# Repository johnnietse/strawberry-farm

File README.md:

# 🌿 G.O.S. - Greenhouse Operating System
## High-Throughput Plant Phenotyping Platform

**Illuminate & Automate: Reinforcement Learning + IoT Sensor Array for LED-Steered Transpiration in Greenhouse Strawberries**

---

## 📋 Table of Contents

1. [What is G.O.S.?](#-what-is-gos)
2. [System Architecture](#-system-architecture)
3. [Data Flow Workflow](#-data-flow-workflow)
4. [Quick Start](#-quick-start)
5. [Testing & Verification](#-testing--verification)
6. [File Reference](#-file-reference)
7. [API Endpoints](#-api-endpoints)
8. [Hardware Integration](#-hardware-integration)

---

## 🎯 What is G.O.S.?

G.O.S. is an **open-source phenotyping platform** that transforms raw greenhouse sensor data into actionable plant insights:

| Feature | Description |
|:---|:---|
| **40 Wireless Nodes** | nRF52840 sensors (Thread mesh) |
| **VPD Calculation** | Real-time vapor pressure deficit |
| **Transpiration** | Penman-Monteith estimation |
| **Stress Detection** | Multi-factor scoring (0-100) |
| **LED Control** | RL-based spectral recommendations |
| **ML Pipeline** | 5-source temporal synchronization |

---

## 🏗️ System Architecture

### Service Topology (12 Docker Containers)

```
┌─────────────────────────────────────────────────────────────┐
│                    USER INTERFACE LAYER                      │
│   Dashboard (:8080)  │  Grafana (:3000)  │  API (:5000)     │
├─────────────────────────────────────────────────────────────┤
│                    DATA STORAGE LAYER                        │
│                   TimescaleDB (:5432)                        │
│  ┌────────────┬────────────┬────────────┬────────────┐      │
│  │raw_telemetry│met_station │research_   │led_schedule│      │
│  │            │_data       │events      │_history    │      │
│  └────────────┴────────────┴────────────┴────────────┘      │
├─────────────────────────────────────────────────────────────┤
│                  PROCESSING LAYER                            │
│  sync_engine │ api │ ml_engine │ biology_engine │ safety    │
├─────────────────────────────────────────────────────────────┤
│                   INGESTION LAYER                            │
│  mqtt_bridge │ ingest (farm_sim) │ met_station              │
├─────────────────────────────────────────────────────────────┤
│                   MESSAGING LAYER                            │
│              Mosquitto MQTT (:1883 / :9001)                  │
├─────────────────────────────────────────────────────────────┤
│                    HARDWARE LAYER                            │
│  Raspberry Pi (OTBR) ─── nRF52840 Nodes (x40) ─── Sensors   │
└─────────────────────────────────────────────────────────────┘
```

### Service Dependencies

```mermaid
graph TD
    DB[TimescaleDB] --> MQTT_BRIDGE[mqtt_bridge]
    DB --> INGEST[ingest/farm_sim]
    DB --> MET[met_station]
    DB --> API[api]
    INGEST --> SYNC[sync_engine]
    MET --> SYNC
    SYNC --> ML[ml_engine]
    BIO[biology_engine] --> ML
    MQTT[Mosquitto] --> MQTT_BRIDGE
    API --> DASH[dashboard]
    DB --> GRAFANA[Grafana]
```

---

## 🔄 Data Flow Workflow

### Step-by-Step Data Journey

```
1. SENSOR LAYER
   └── nRF52 nodes collect: temp, humidity, PAR, battery
   └── Transmit via CoAP/Thread to Raspberry Pi

2. GATEWAY LAYER
   └── Raspberry Pi runs OTBR (OpenThread Border Router)
   └── Translates Thread → MQTT
   └── Publishes to Mosquitto broker

3. INGESTION LAYER
   └── mqtt_bridge.py subscribes to MQTT topics
   └── Validates JSON payload
   └── Inserts into raw_telemetry table

4. METEOROLOGICAL LAYER
   └── met_station.py logs pyranometer + spectrometer data
   └── Writes to met_station_data table

5. SYNCHRONIZATION LAYER
   └── sync.py runs every 5 minutes
   └── Performs 5-source temporal joins:
       ├── raw_telemetry (hardware)
       ├── met_station_data (environment)
       ├── led_schedule_history (light control)
       ├── research_events (annotations)
       └── yield_logs (harvest data)
   └── Outputs curated_research_dataset.csv

6. PHENOTYPING LAYER
   └── api.py exposes /api/phenotype endpoint
   └── Calculates VPD, transpiration, stress in real-time
   └── Returns LED recommendations

7. ML LAYER
   └── agent_rl.py loads curated dataset
   └── Trains/runs RL policy for LED optimization
   └── biology_engine provides physics constraints

8. VISUALIZATION LAYER
   └── dashboard/ displays real-time data
   └── Grafana provides monitoring dashboards
   └── LLM assistant enables natural language queries
```

---

## 🚀 Quick Start

### Prerequisites
- Docker Desktop 24+
- Python 3.11+
- 8GB RAM minimum

### Installation

```bash
# Clone repository
git clone https://github.com/queensu-epower/gos.git
cd Stawberry_Farm

# Windows setup
.\setup.bat

# OR manual setup
python -m venv .venv
.venv\Scripts\activate
pip install -r requirements.txt
```

### Running the System

```bash
# Start all 12 services
python run.py --up

# Check service status
python run.py --status

# View sync engine logs
python run.py --logs backbone

# View ML engine logs
python run.py --logs ai

# Stop all services
python run.py --down

# Clean (removes all data!)
python run.py --clean
```

### Access Points

| Service | URL | Credentials |
|:---|:---|:---|
| Dashboard | http://localhost:8080 | — |
| Grafana | http://localhost:3000 | admin / (see .env) |

| API | http://localhost:5000 | — |
| Database | localhost:5432 | researcher / (see .env) |

| MQTT | localhost:1883 | — |

---

## 🧪 Testing & Verification

### 1. Verify Docker Services

```bash
# Check all containers are running
docker compose ps

# Expected: 12 services with "Up" status
```

### 2. Test Database Connection

```bash
# Connect to database
docker exec -it stawberry_farm-db-1 psql -U researcher -d strawberry_research

# Check tables exist
\dt

# Query sample data
SELECT COUNT(*) FROM raw_telemetry;
SELECT * FROM raw_telemetry ORDER BY time DESC LIMIT 5;
```

### 3. Test API Endpoints

```bash
# Get node status
curl http://localhost:5000/api/nodes

# Calculate phenotype
curl -X POST http://localhost:5000/api/phenotype \
  -H "Content-Type: application/json" \
  -d '{"temp_c": 25.0, "humidity_pct": 65.0, "par_umol": 800.0}'

# Get phenotype summary
curl http://localhost:5000/api/phenotype/summary

# Log a research event
curl -X POST http://localhost:5000/api/event \
  -H "Content-Type: application/json" \
  -d '{"type": "pest", "description": "Spider mites on row 3", "severity": 2}'
```

### 4. Test Data Pipeline

```bash
# Wait 5 minutes for sync cycle, then check:
ls -la data/

# Should see: curated_research_dataset.csv
```

### 5. Test MQTT (Real Hardware)

```bash
# Subscribe to all topics
mosquitto_sub -h localhost -t "gos/#" -v

# Publish test message
mosquitto_pub -h localhost -t "gos/node/test01/telemetry" \
  -m '{"temp_c": 24.5, "humidity_pct": 62.0, "par_umol": 750}'
```

---

## 📂 File Reference

### Root Directory

| File | Purpose |
|:---|:---|
| `docker-compose.yml` | Orchestrates 12 Docker services |
| `run.py` | CLI tool for system management |
| `setup.bat` | Windows environment setup |
| `requirements.txt` | Python dependencies |
| `.env.example` | Environment variable template |

### gateway/ - Data Backbone Services

| File | Purpose | Writes To |
|:---|:---|:---|
| `schema.sql` | Database schema (6 hypertables) | TimescaleDB |
| `services/sync.py` | 5-source temporal joins | `data/curated_*.csv` |
| `services/api.py` | REST API + phenotype endpoints | — |
| `services/mqtt_bridge.py` | MQTT → Database | `raw_telemetry` |
| `services/farm_sim.py` | 40-node sensor simulation | `raw_telemetry` |
| `services/met_station.py` | Met station simulation | `met_station_data` |
| `services/otbr_gateway.py` | OpenThread helper | — |
| `services/mqtt_sn_bridge.py` | MQTT-SN for nRF52 | — |
| `services/safety_ltl.py` | LTL safety monitor | — |
| `Dockerfile` | Container build | — |
| `requirements.txt` | Python deps | — |

### ml_engine/ - Machine Learning

| File | Purpose | Input | Output |
|:---|:---|:---|:---|
| `phenotyping.py` | VPD, transpiration, stress | Sensor data | Phenotype metrics |
| `plant_sim_c3.py` | FvCB photosynthesis model | T, CO2, PAR | Assimilation rate |
| `agent_rl.py` | LED control RL agent | Curated CSV | LED recommendations |
| `spectral_opt.py` | Spectral optimization | LED params | Optimal ratios |
| `macq_learner.py` | Action model learning | Trace data | PDDL actions |
| `domain.pddl` | AI planning domain | — | — |

### firmware/ - nRF52840 Embedded Code

| File | Purpose |
|:---|:---|
| `src/main.c` | Main firmware (Zephyr RTOS + CoAP) |
| `prj.conf` | Zephyr config (SED mode, sensors) |
| `CMakeLists.txt` | Build system |
| `boards/nrf52840_phytotron.overlay` | Device tree (I2C, PWM, ADC) |
| `drivers/led_control.c` | PWM LED driver |
| `include/*.h` | Header files (7 files) |

### dashboard/ - Web GUI

| File | Purpose |
|:---|:---|
| `index.html` | Main UI |
| `css/style.css` | Styling |
| `js/dashboard.js` | Data fetching, node display |
| `js/llm_assistant.js` | LLM chat for event annotation |

### monitoring/ - Observability

| File | Purpose |
|:---|:---|
| `grafana/provisioning/datasources/timescaledb.yml` | Grafana → DB connection |
| `mosquitto/config/mosquitto.conf` | MQTT broker config |

### documentation/ - Hardware Guides

| File | Purpose |
|:---|:---|
| `raspberry_pi_setup.md` | OTBR installation |
| `nrf52840_pinout.md` | Soldering guide |
| `hardware_specs.md` | PCB, enclosure specs |
| `bench_testing.md` | Validation procedures |
| `hardware_protocol.md` | Communication protocol |
| `requirements.md` | ELEC 490/498 checklist |

---

## 📡 API Endpoints

### Phenotyping

| Method | Endpoint | Description |
|:---|:---|:---|
| POST | `/api/phenotype` | Calculate VPD, transpiration, stress from sensor data |
| GET | `/api/phenotype/summary` | Greenhouse-wide summary (last hour) |

### Data Input (Group 2 GUI)

| Method | Endpoint | Description |
|:---|:---|:---|
| POST | `/api/event` | Log research event (pest, fertilizer, equipment) |
| POST | `/api/yield` | Log harvest yield data |
| POST | `/api/led` | Update LED schedule |

### Data Output

| Method | Endpoint | Description |
|:---|:---|:---|
| GET | `/api/nodes` | Get all node status |
| GET | `/api/events` | Get recent events |
| GET | `/api/curated` | Download ML-ready dataset (CSV) |

### Health

| Method | Endpoint | Description |
|:---|:---|:---|
| GET | `/health` | Service health check |

---

## 🔧 Hardware Integration

### For Real Hardware Deployment

1. **Raspberry Pi Setup**
   ```bash
   # See documentation/raspberry_pi_setup.md
   # Install OTBR, flash nRF52840 dongle
   ```

2. **Flash nRF52 Nodes**
   ```bash
   cd firmware
   west build -b nrf52840dk_nrf52840
   west flash
   ```

3. **Update docker-compose.yml**
   - Comment out `ingest` service (simulation)
   - `mqtt_bridge` will handle real MQTT data

4. **Configure MQTT Topics**
   - Nodes publish to: `gos/node/{node_id}/telemetry`
   - Met station publishes to: `gos/met/data`

---

## Requirements, Implementation, and Status

| Requirement | Implementation | Status |
|:---|:---|:---:|
| Data backbone pipeline | `sync.py` - 5-source joins | ✅ |
| PostgreSQL database | TimescaleDB hypertables | ✅ |
| Docker orchestration | 12-service compose | ✅ |
| 40 wireless nodes | Thread mesh | ✅ |
| Preserved sample identity | EUI64 in all tables | ✅ |
| Group 2 GUI | Dashboard + LLM | ✅ |
| ML-ready datasets | `/api/curated` | ✅ |
| Phenotyping | VPD, transpiration | ✅ |
| RL model (stretch) | `agent_rl.py` | ✅ |

---

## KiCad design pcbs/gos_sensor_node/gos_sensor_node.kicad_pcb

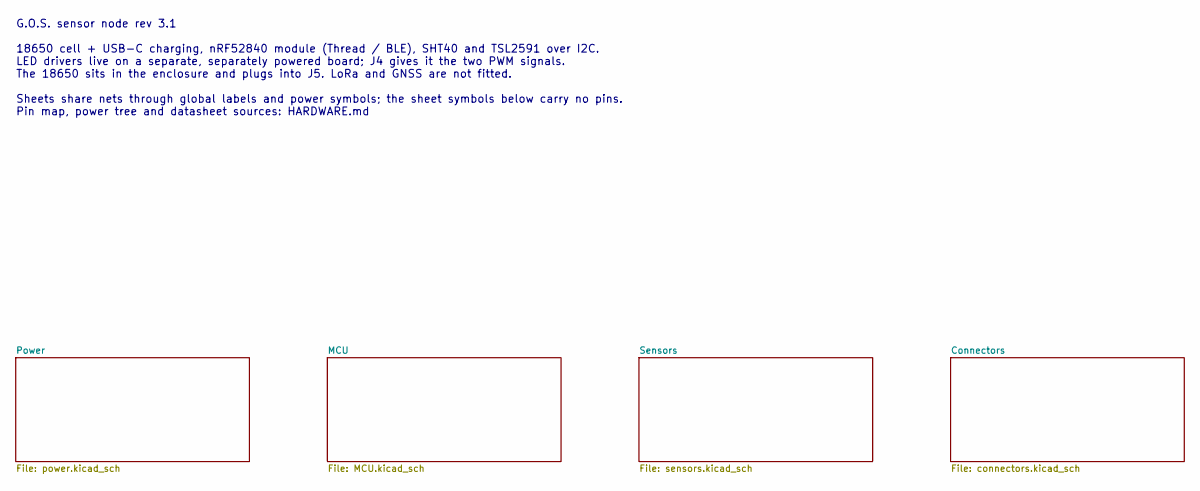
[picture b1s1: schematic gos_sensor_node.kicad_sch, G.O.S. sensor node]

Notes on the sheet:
G.O.S. sensor node rev 3.1 18650 cell + USB-C charging, nRF52840 module (Thread / BLE), SHT40 and TSL2591 over I2C. LED drivers live on a separate, separately powered board; J4 gives it the two PWM signals. The 18650 sits in the enclosure and plugs into J5. LoRa and GNSS are not fitted. Sheets shar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

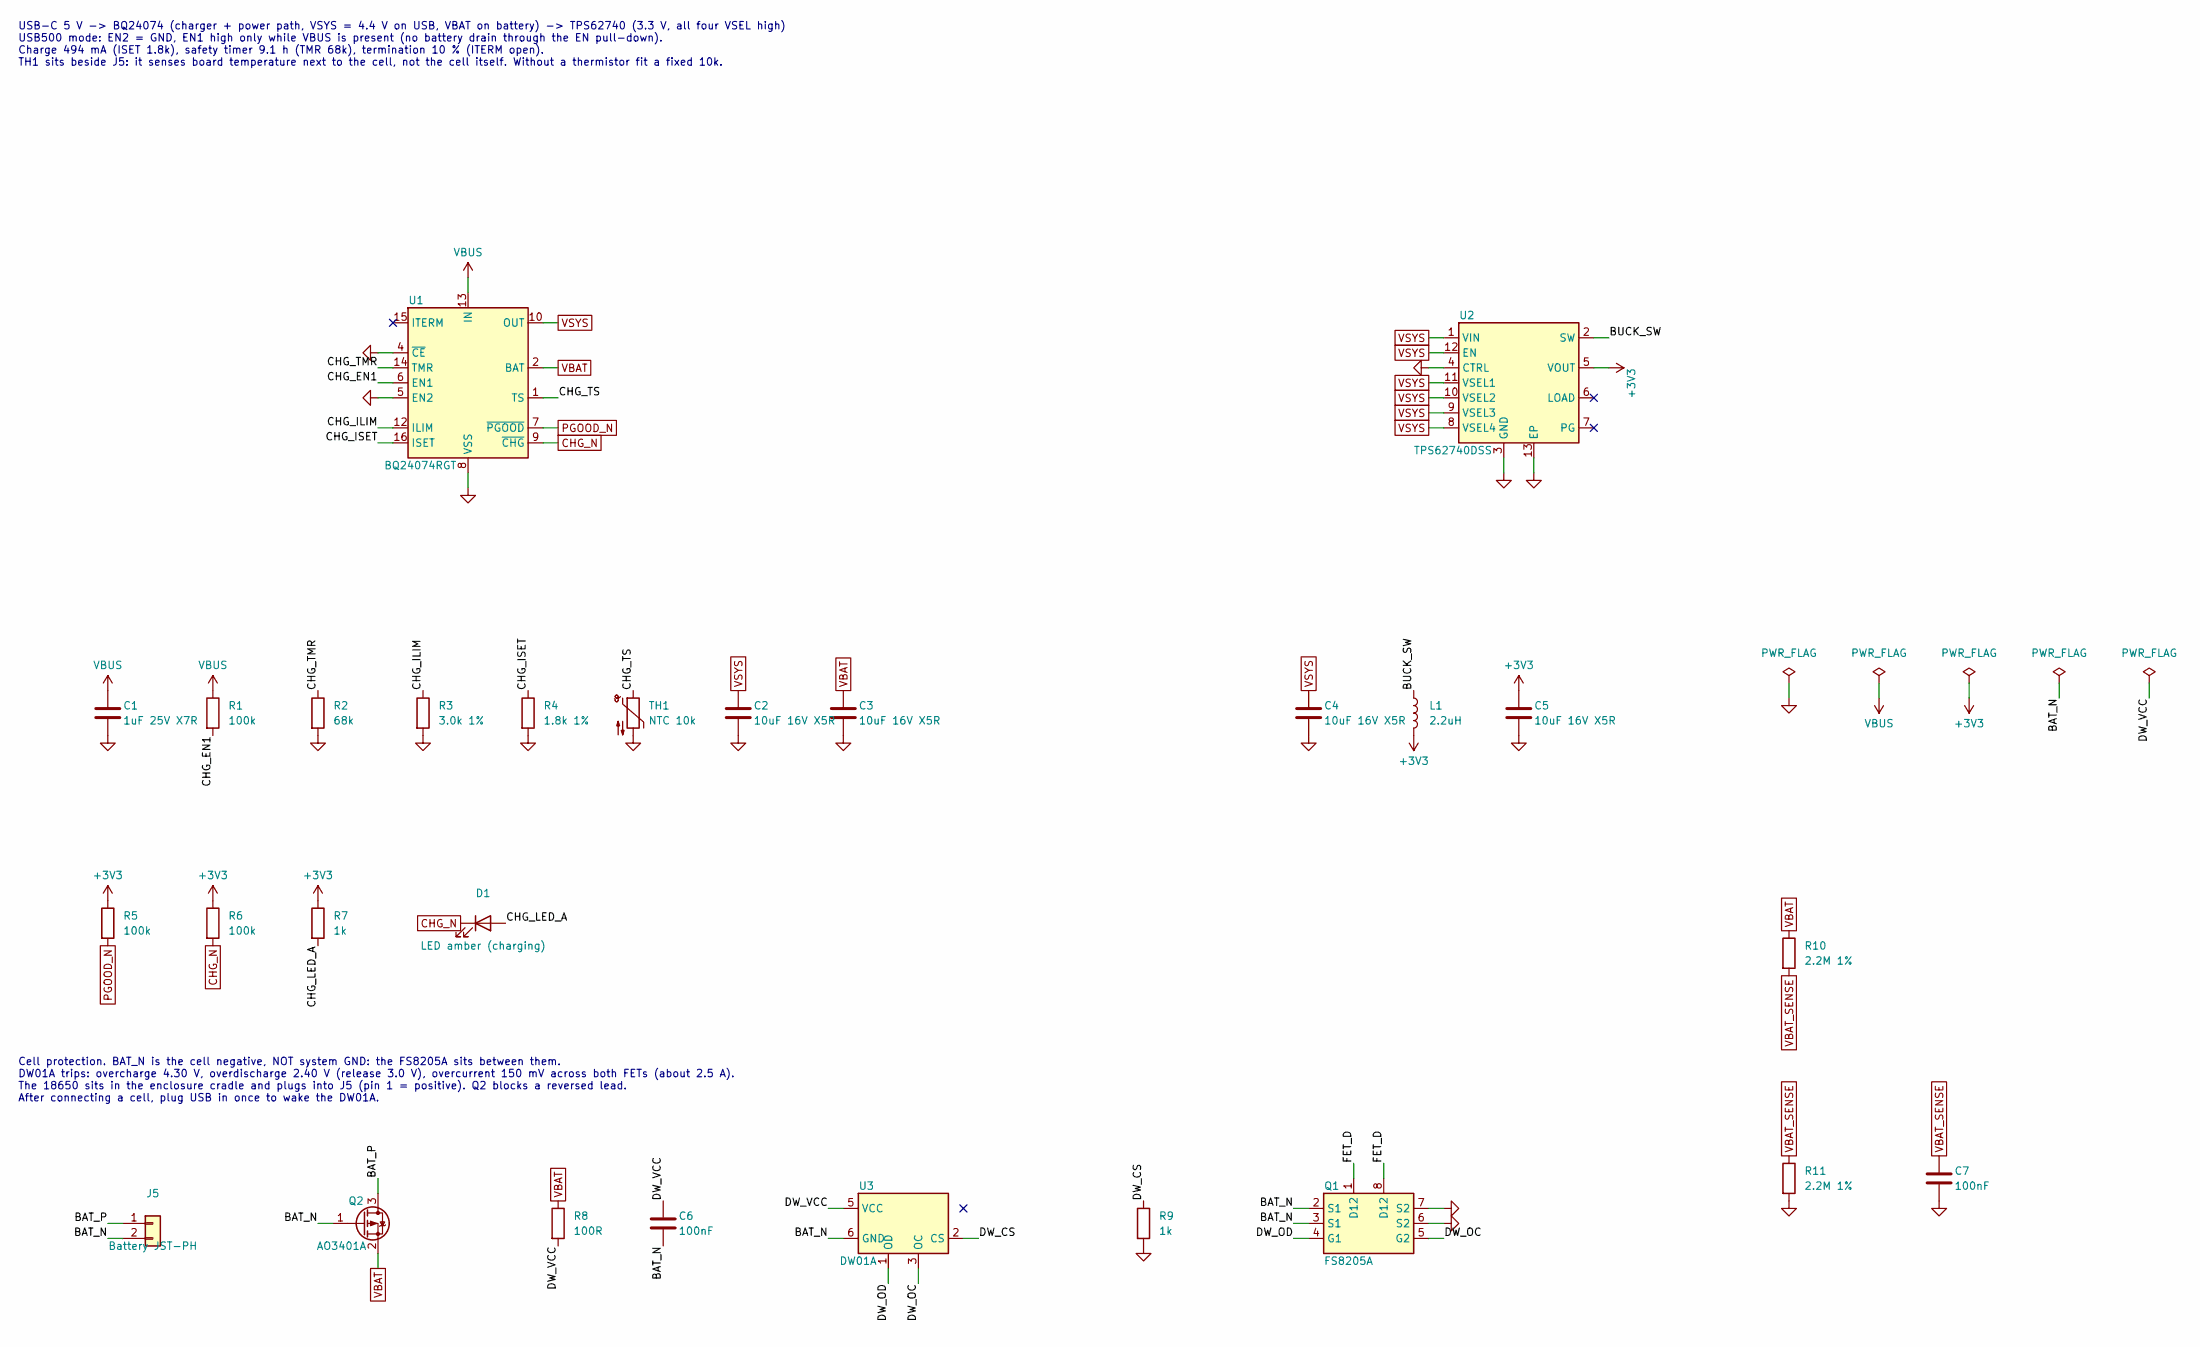
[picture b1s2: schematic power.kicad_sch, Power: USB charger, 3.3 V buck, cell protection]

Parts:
C1: 1uF 25V X7R; C_0603_1608Metric
C2, C3, C4, C5: 10uF 16V X5R; C_0805_2012Metric
C6, C7: 100nF; C_0603_1608Metric
D1: LED amber (charging); LED_0603_1608Metric
J5: Battery JST-PH; JST_PH_S2B-PH-K_1x02_P2.00mm_Horizontal; MPN S2B-PH-K-S
L1: 2.2uH; L_Coilcraft_LPS3314
Q1: FS8205A; TSSOP-8_4.4x3mm_P0.65mm; MPN FS8205A
Q2: AO3401A; SOT-23; MPN AO3401A
R1, R5, R6: 100k; R_0603_1608Metric
R2: 68k; R_0603_1608Metric
R3: 3.0k 1%; R_0603_1608Metric
R4: 1.8k 1%; R_0603_1608Metric
R7, R9: 1k; R_0603_1608Metric
R8: 100R; R_0603_1608Metric
R10, R11: 2.2M 1%; R_0603_1608Metric
TH1: NTC 10k; R_0603_1608Metric
U1: BQ24074RGT; VQFN-16-1EP_3x3mm_P0.5mm_EP1.6x1.6mm; MPN BQ24074RGTR
U2: TPS62740DSS; WSON-12-1EP_3x2mm_P0.5mm_EP1x2.65; MPN TPS62740DSSR
U3: DW01A; SOT-23-6; MPN DW01A

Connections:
+3V3: C5.1, L1.2, R5.1, R6.1, R7.1, U2.5 (VOUT); also elsewhere on the board
/Power/BAT_N: C6.2, J5.2, Q1.2 (S1), Q1.3 (S1), Q2.1 (G), U3.6 (GND)
/Power/BAT_P: J5.1, Q2.3 (D)
/Power/BUCK_SW: L1.1, U2.2 (SW)
/Power/CHG_EN1: R1.2, U1.6 (EN1)
/Power/CHG_ILIM: R3.1, U1.12 (ILIM)
/Power/CHG_ISET: R4.1, U1.16 (ISET)
/Power/CHG_LED_A: D1.2 (A), R7.2
/Power/CHG_TMR: R2.1, U1.14 (TMR)
/Power/CHG_TS: TH1.1, U1.1 (TS)
/Power/DW_CS: R9.1, U3.2 (CS)
/Power/DW_OC: Q1.5 (G2), U3.3 (OC)
/Power/DW_OD: Q1.4 (G1), U3.1 (OD)
/Power/DW_VCC: C6.1, R8.2, U3.5 (VCC)
/Power/FET_D: Q1.1 (D12), Q1.8 (D12)
CHG_N: D1.1 (K), R6.2, U1.9 (~CHG); also elsewhere on the board
GND: C1.2, C2.2, C3.2, C4.2, C5.2, C7.2, Q1.6 (S2), Q1.7 (S2), R2.2, R3.2, R4.2, R9.2, R11.2, TH1.2, U1.4 (~CE), U1.5 (EN2), U1.8 (VSS), U1.17 (VSS), U2.3 (GND), U2.4 (CTRL), U2.13 (EP); also elsewhere on the board
PGOOD_N: R5.2, U1.7 (~PGOOD); also elsewhere on the board
VBAT: C3.1, Q2.2 (S), R8.1, R10.1, U1.2 (BAT), U1.3 (BAT); also elsewhere on the board
VBAT_SENSE: C7.1, R10.2, R11.1; also elsewhere on the board
VBUS: C1.1, R1.1, U1.13 (IN); also elsewhere on the board
VSYS: C2.1, C4.1, U1.10 (OUT), U1.11 (OUT), U2.1 (VIN), U2.8 (VSEL4), U2.9 (VSEL3), U2.10 (VSEL2), U2.11 (VSEL1), U2.12 (EN); also elsewhere on the board

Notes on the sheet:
USB-C 5 V -> BQ24074 (charger + power path, VSYS = 4.4 V on USB, VBAT on battery) -> TPS62740 (3.3 V, all four VSEL high) USB500 mode: EN2 = GND, EN1 high only while VBUS is present (no battery drain through the EN pull-down). Charge 494 mA (ISET 1.8k), safety timer 9.1 h (TMR 68k), termination 10 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
Cell protection. BAT_N is the cell negative, NOT system GND: the FS8205A sits between them. DW01A trips: overcharge 4.30 V, overdischarge 2.40 V (release 3.0 V), overcurrent 150 mV across both FETs (about 2.5 A). The 18650 sits in the enclosure cradle and plugs into J5 (pin 1 = positive). Q2 blocks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

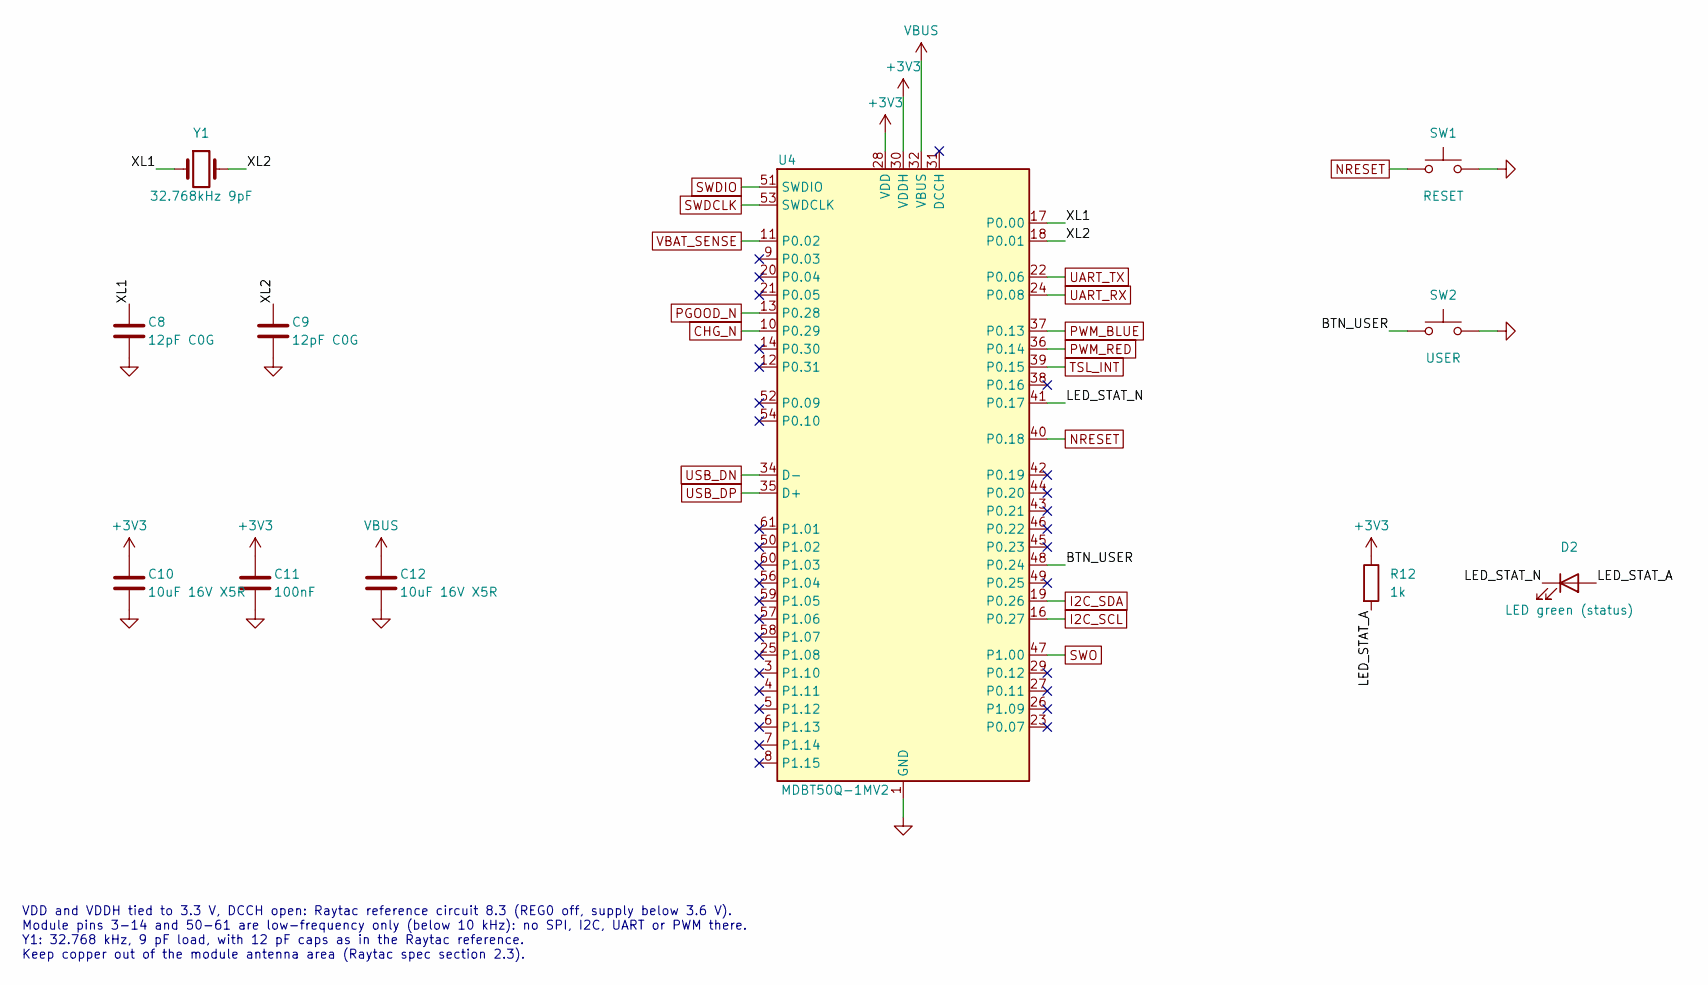
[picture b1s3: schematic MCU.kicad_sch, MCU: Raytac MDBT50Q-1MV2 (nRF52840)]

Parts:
C8, C9: 12pF C0G; C_0603_1608Metric
C10, C12: 10uF 16V X5R; C_0805_2012Metric
C11: 100nF; C_0603_1608Metric
D2: LED green (status); LED_0603_1608Metric
R12: 1k; R_0603_1608Metric
SW1: RESET; SW_SPST_B3U-1000P; MPN B3U-1000P
SW2: USER; SW_SPST_B3U-1000P; MPN B3U-1000P
U4: MDBT50Q-1MV2; Raytac_MDBT50Q; MPN MDBT50Q-1MV2
Y1: 32.768kHz 9pF; Crystal_SMD_3215-2Pin_3.2x1.5mm; MPN ABS07-32.768KHZ-9-T

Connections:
+3V3: C10.1, C11.1, R12.1, U4.28 (VDD), U4.30 (VDDH); also elsewhere on the board
/MCU/BTN_USER: SW2.1, U4.48 (P0.24)
/MCU/LED_STAT_A: D2.2 (A), R12.2
/MCU/LED_STAT_N: D2.1 (K), U4.41 (P0.17)
/MCU/XL1: C8.1, U4.17 (P0.00), Y1.1
/MCU/XL2: C9.1, U4.18 (P0.01), Y1.2
CHG_N: U4.10 (P0.29); also elsewhere on the board
GND: C8.2, C9.2, C10.2, C11.2, C12.2, SW1.2, SW2.2, U4.1 (GND), U4.2 (GND), U4.15 (GND), U4.33 (GND), U4.55 (GND); also elsewhere on the board
I2C_SCL: U4.16 (P0.27); also elsewhere on the board
I2C_SDA: U4.19 (P0.26); also elsewhere on the board
NRESET: SW1.1, U4.40 (P0.18); also elsewhere on the board
PGOOD_N: U4.13 (P0.28); also elsewhere on the board
PWM_BLUE: U4.37 (P0.13); also elsewhere on the board
PWM_RED: U4.36 (P0.14); also elsewhere on the board
SWDCLK: U4.53 (SWDCLK); also elsewhere on the board
SWDIO: U4.51 (SWDIO); also elsewhere on the board
SWO: U4.47 (P1.00); also elsewhere on the board
TSL_INT: U4.39 (P0.15); also elsewhere on the board
UART_RX: U4.24 (P0.08); also elsewhere on the board
UART_TX: U4.22 (P0.06); also elsewhere on the board
USB_DN: U4.34 (D-); also elsewhere on the board
USB_DP: U4.35 (D+); also elsewhere on the board
VBAT_SENSE: U4.11 (P0.02); also elsewhere on the board
VBUS: C12.1, U4.32 (VBUS); also elsewhere on the board

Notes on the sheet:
VDD and VDDH tied to 3.3 V, DCCH open: Raytac reference circuit 8.3 (REG0 off, supply below 3.6 V). Module pins 3-14 and 50-61 are low-frequency only (below 10 kHz): no SPI, I2C, UART or PWM there. Y1: 32.768 kHz, 9 pF load, with 12 pF caps as in the Raytac reference. Keep copper out of the module 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

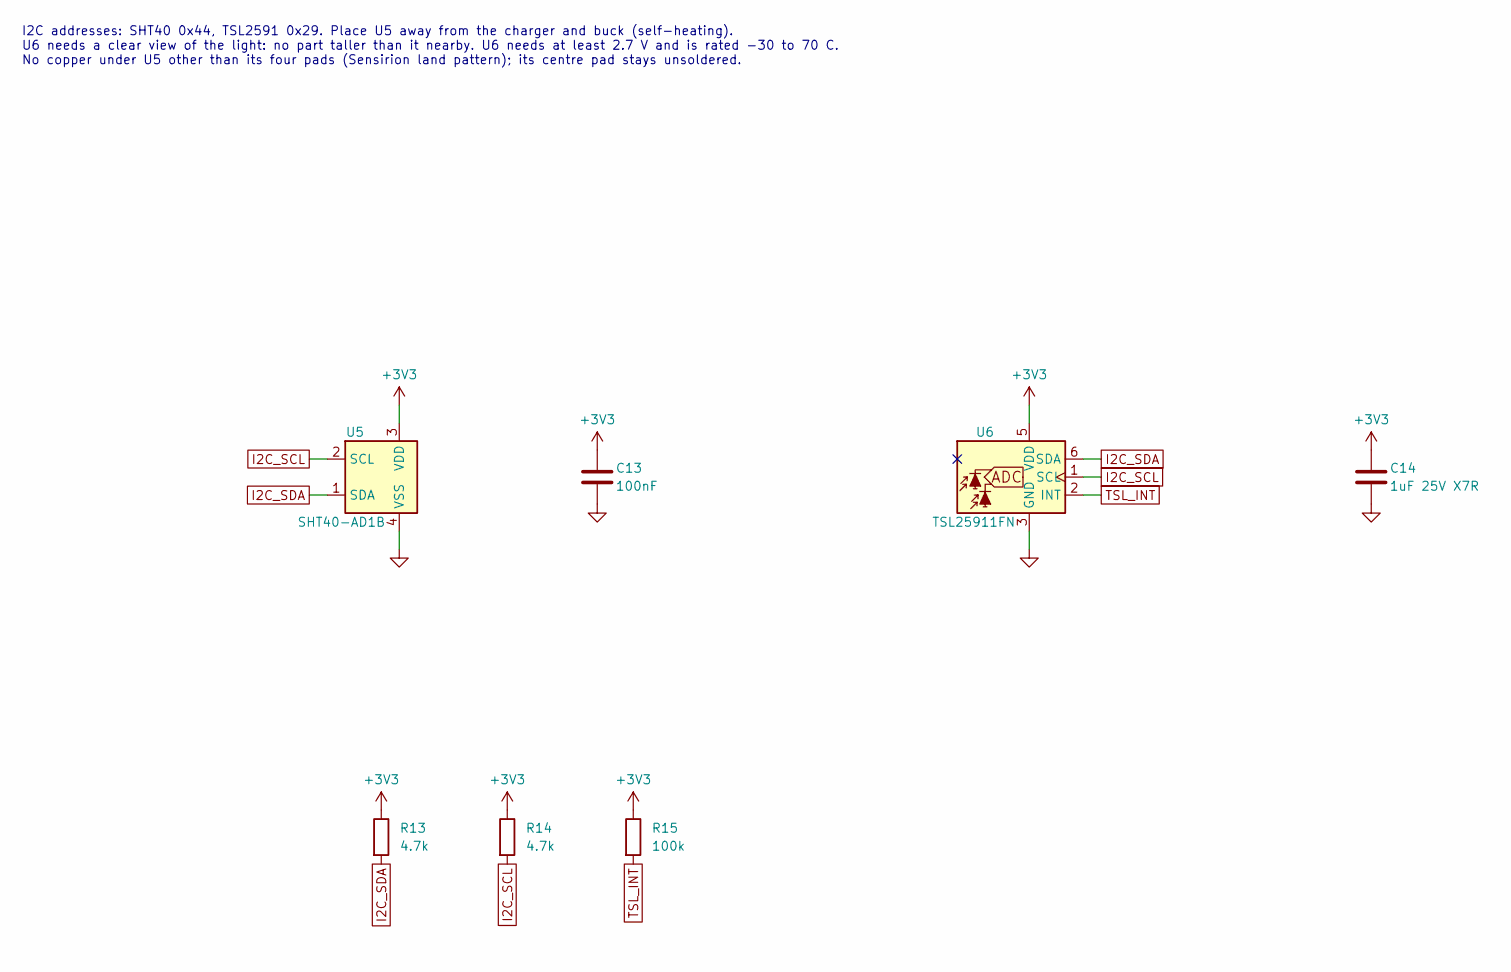
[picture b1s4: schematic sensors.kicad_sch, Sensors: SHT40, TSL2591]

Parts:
C13: 100nF; C_0603_1608Metric
C14: 1uF 25V X7R; C_0603_1608Metric
R13, R14: 4.7k; R_0603_1608Metric
R15: 100k; R_0603_1608Metric
U5: SHT40-AD1B; Sensirion_DFN-4_1.5x1.5mm_P0.8mm_SHT4x_NoCentralPad; MPN SHT40-AD1B-R2
U6: TSL25911FN; AMS_TSL25911FN; MPN TSL25911FN

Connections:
+3V3: C13.1, C14.1, R13.1, R14.1, R15.1, U5.3 (VDD), U6.5 (VDD); also elsewhere on the board
GND: C13.2, C14.2, U5.4 (VSS), U6.3 (GND); also elsewhere on the board
I2C_SCL: R14.2, U5.2 (SCL), U6.1 (SCL); also elsewhere on the board
I2C_SDA: R13.2, U5.1 (SDA), U6.6 (SDA); also elsewhere on the board
TSL_INT: R15.2, U6.2 (INT); also elsewhere on the board

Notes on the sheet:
I2C addresses: SHT40 0x44, TSL2591 0x29. Place U5 away from the charger and buck (self-heating). U6 needs a clear view of the light: no part taller than it nearby. U6 needs at least 2.7 V and is rated -30 to 70 C. No copper under U5 other than its four pads (Sensirion land pattern); its centre pad 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

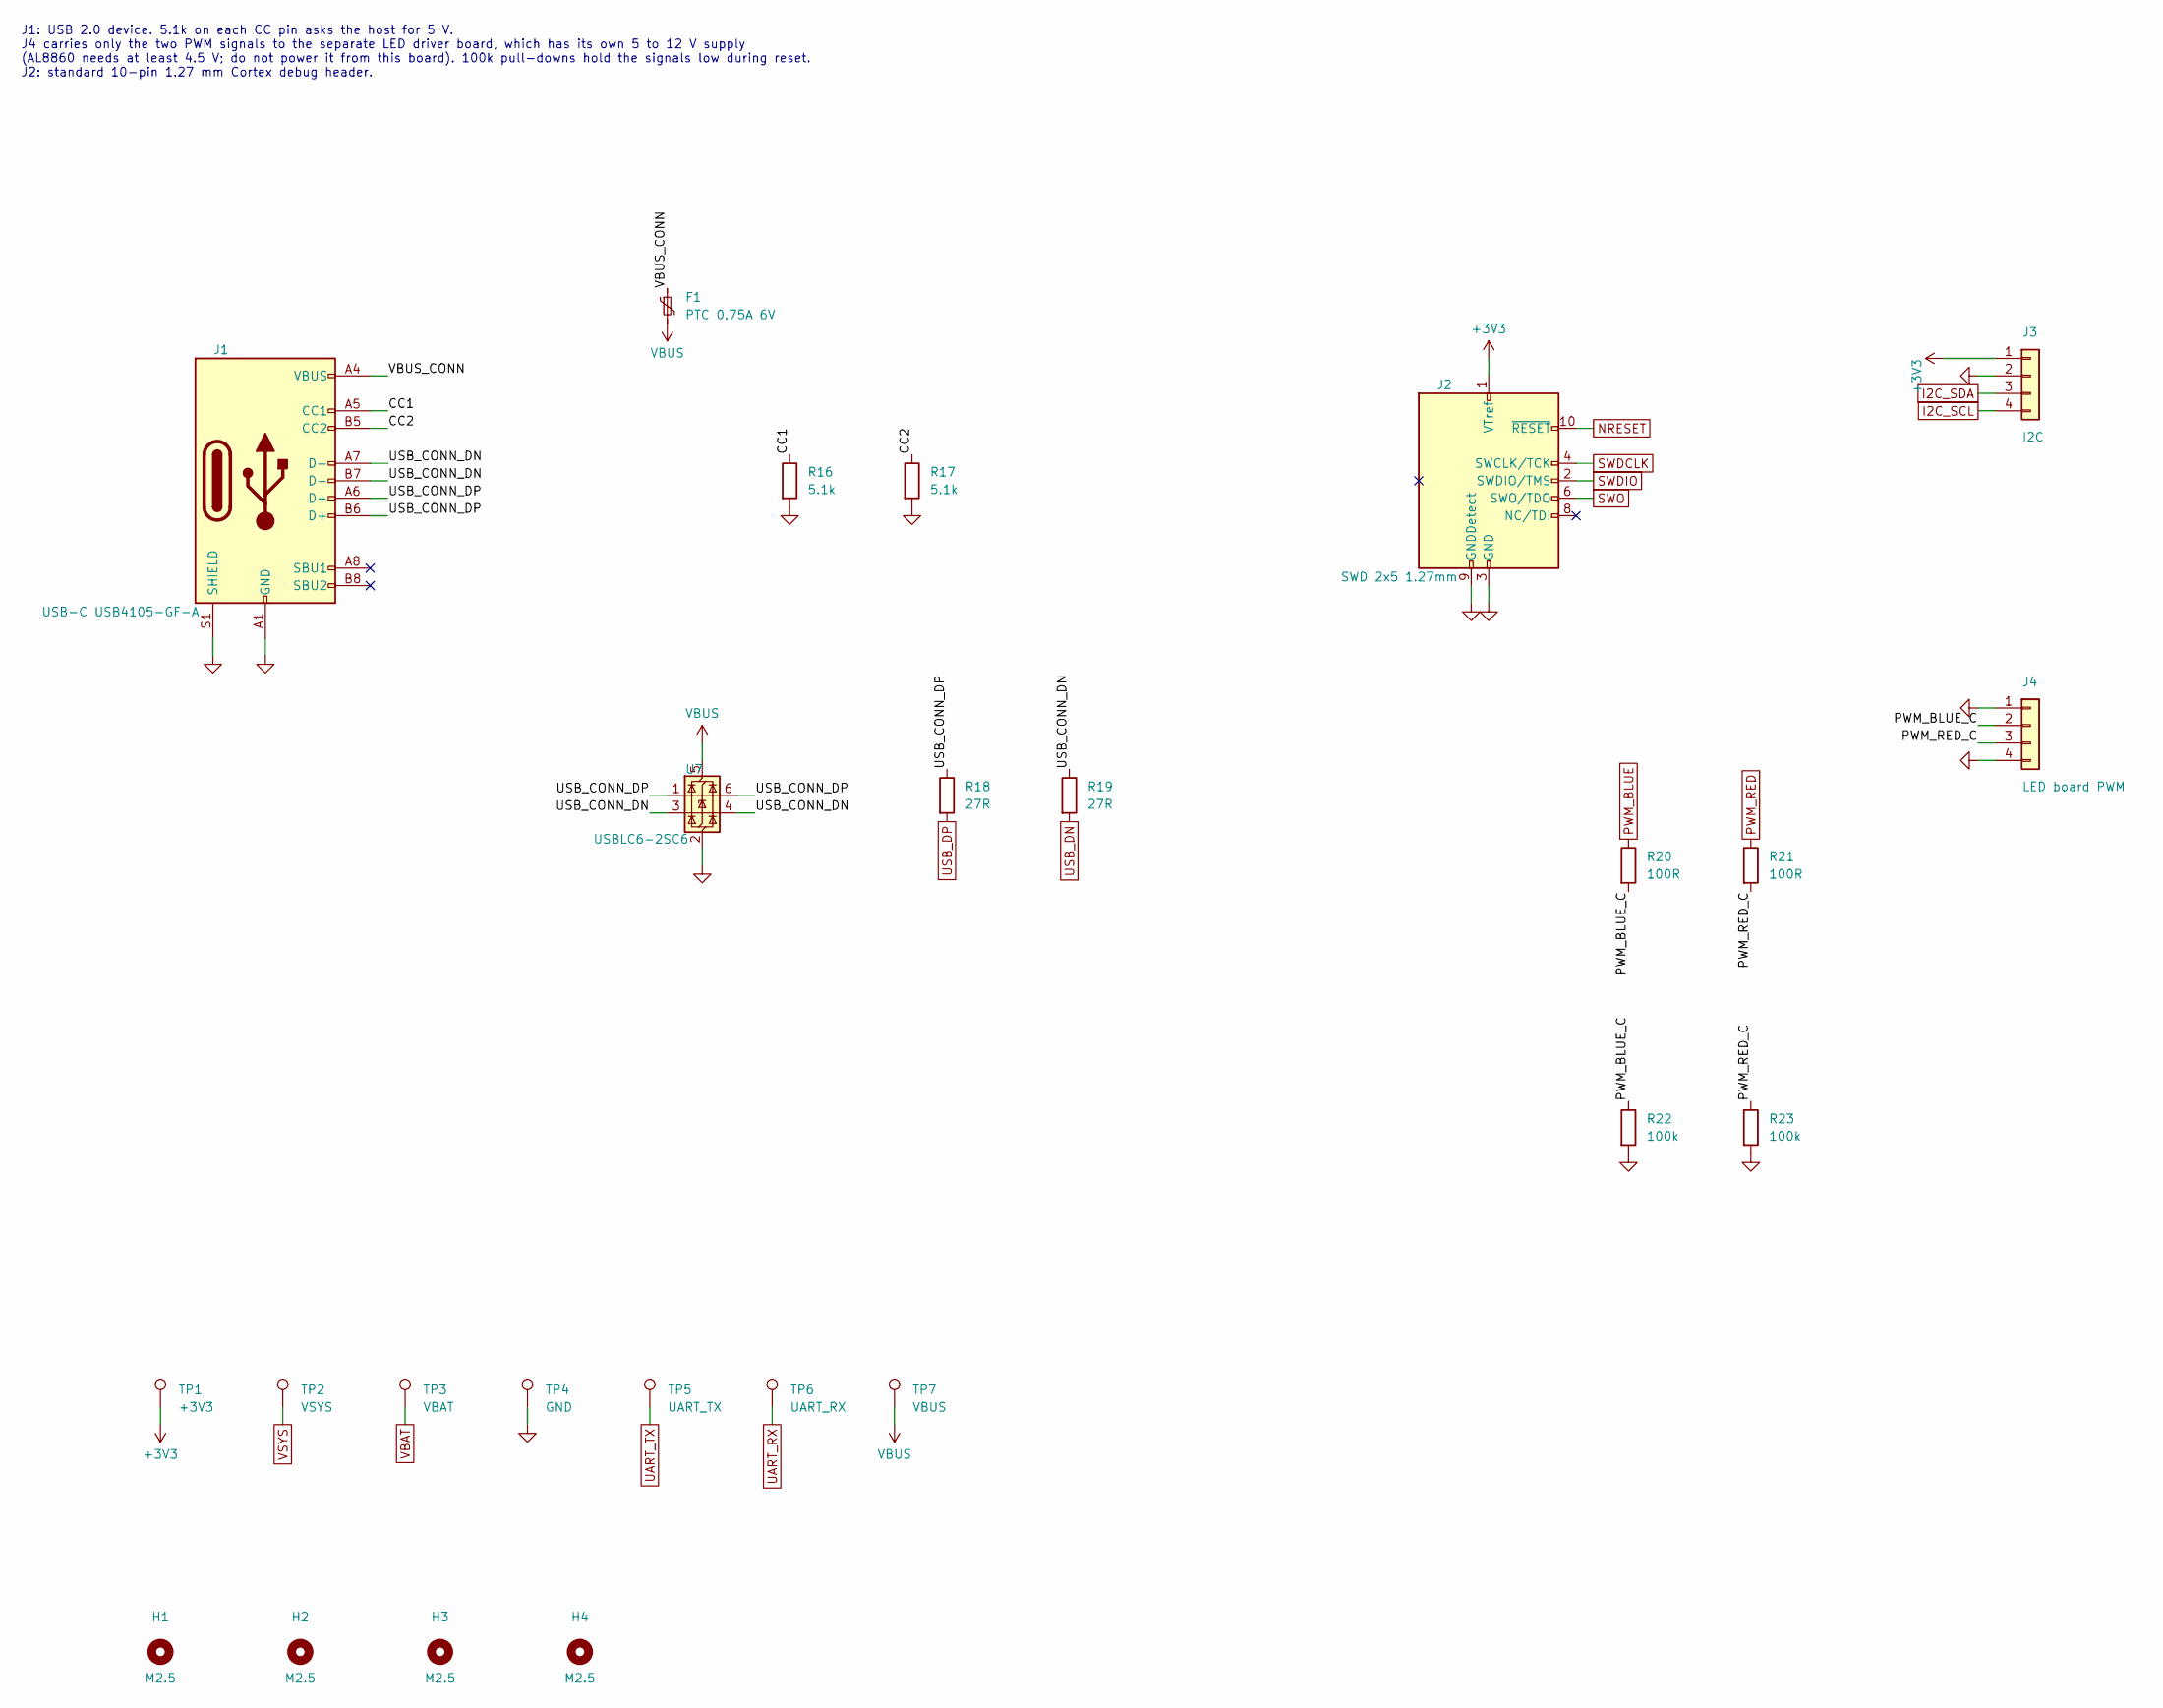
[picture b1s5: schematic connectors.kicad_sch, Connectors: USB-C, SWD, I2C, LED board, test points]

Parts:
F1: PTC 0.75A 6V; Fuse_1206_3216Metric
H1, H2, H3, H4: M2.5; MountingHole_2.7mm_M2.5
J1: USB-C USB4105-GF-A; USB_C_Receptacle_GCT_USB4105-xx-A_16P_TopMnt_Horizontal; MPN USB4105-GF-A
J2: SWD 2x5 1.27mm; PinHeader_2x05_P1.27mm_Vertical_SMD
J3: I2C; PinHeader_1x04_P2.54mm_Vertical
J4: LED board PWM; PinHeader_1x04_P2.54mm_Vertical
R16, R17: 5.1k; R_0603_1608Metric
R18, R19: 27R; R_0603_1608Metric
R20, R21: 100R; R_0603_1608Metric
R22, R23: 100k; R_0603_1608Metric
TP1: +3V3; TestPoint_Pad_D1.0mm
TP2: VSYS; TestPoint_Pad_D1.0mm
TP3: VBAT; TestPoint_Pad_D1.0mm
TP4: GND; TestPoint_Pad_D1.0mm
TP5: UART_TX; TestPoint_Pad_D1.0mm
TP6: UART_RX; TestPoint_Pad_D1.0mm
TP7: VBUS; TestPoint_Pad_D1.0mm
U7: USBLC6-2SC6; SOT-23-6; MPN USBLC6-2SC6

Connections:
+3V3: J2.1 (VTref), J3.1, TP1.1; also elsewhere on the board
/Connectors/CC1: J1.A5 (CC1), R16.1
/Connectors/CC2: J1.B5 (CC2), R17.1
/Connectors/PWM_BLUE_C: J4.2, R20.2, R22.1
/Connectors/PWM_RED_C: J4.3, R21.2, R23.1
/Connectors/USB_CONN_DN: J1.A7 (D-), J1.B7 (D-), R19.1, U7.3 (I/O2), U7.4 (I/O2)
/Connectors/USB_CONN_DP: J1.A6 (D+), J1.B6 (D+), R18.1, U7.1 (I/O1), U7.6 (I/O1)
/Connectors/VBUS_CONN: F1.1, J1.A4 (VBUS), J1.A9 (VBUS), J1.B4 (VBUS), J1.B9 (VBUS)
GND: J1.A1 (GND), J1.A12 (GND), J1.B1 (GND), J1.B12 (GND), J1.S1 (SHIELD), J2.3 (GND), J2.5 (GND), J2.9 (GNDDetect), J3.2, J4.1, J4.4, R16.2, R17.2, R22.2, R23.2, TP4.1, U7.2 (GND); also elsewhere on the board
I2C_SCL: J3.4; also elsewhere on the board
I2C_SDA: J3.3; also elsewhere on the board
NRESET: J2.10 (~RESET); also elsewhere on the board
PWM_BLUE: R20.1; also elsewhere on the board
PWM_RED: R21.1; also elsewhere on the board
SWDCLK: J2.4 (SWCLK/TCK); also elsewhere on the board
SWDIO: J2.2 (SWDIO/TMS); also elsewhere on the board
SWO: J2.6 (SWO/TDO); also elsewhere on the board
UART_RX: TP6.1; also elsewhere on the board
UART_TX: TP5.1; also elsewhere on the board
USB_DN: R19.2; also elsewhere on the board
USB_DP: R18.2; also elsewhere on the board
VBAT: TP3.1; also elsewhere on the board
VBUS: F1.2, TP7.1, U7.5 (VBUS); also elsewhere on the board
VSYS: TP2.1; also elsewhere on the board

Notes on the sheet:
J1: USB 2.0 device. 5.1k on each CC pin asks the host for 5 V. J4 carries only the two PWM signals to the separate LED driver board, which has its own 5 to 12 V supply (AL8860 needs at least 4.5 V; do not power it from this board). 100k pull-downs hold the signals low during reset. J2: standard 10-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

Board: 2 copper layers, 70 parts (0 on the bottom side), 47 nets, no tracks yet.

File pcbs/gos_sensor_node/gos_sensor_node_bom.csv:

"Refs","Qty","Value","Footprint","Manufacturer","MPN","Description"
"C1,C14","2","1uF 25V X7R","Capacitor_SMD:C_0603_1608Metric","","","Unpolarized capacitor"
"C2,C3,C4,C5,C10,C12","6","10uF 16V X5R","Capacitor_SMD:C_0805_2012Metric","","","Unpolarized capacitor"
"C6,C7,C11,C13","4","100nF","Capacitor_SMD:C_0603_1608Metric","","","Unpolarized capacitor"
"C8,C9","2","12pF C0G","Capacitor_SMD:C_0603_1608Metric","","","Unpolarized capacitor"
"D1","1","LED amber (charging)","LED_SMD:LED_0603_1608Metric","","","Light emitting diode"
"D2","1","LED green (status)","LED_SMD:LED_0603_1608Metric","","","Light emitting diode"
"F1","1","PTC 0.75A 6V","Fuse:Fuse_1206_3216Metric","","","Resettable fuse, polymeric positive temperature coefficient, small symbol"
"J1","1","USB-C USB4105-GF-A","Connector_USB:USB_C_Receptacle_GCT_USB4105-xx-A_16P_TopMnt_Horizontal","GCT","USB4105-GF-A","USB 2.0-only 16P Type-C Receptacle connector"
"J2","1","SWD 2x5 1.27mm","Connector_PinHeader_1.27mm:PinHeader_2x05_P1.27mm_Vertical_SMD","","","Cortex Debug Connector, standard ARM Cortex-M SWD and JTAG interface"
"J3","1","I2C","Connector_PinHeader_2.54mm:PinHeader_1x04_P2.54mm_Vertical","","","Generic connector, single row, 01x04, script generated (kicad-library-utils/schlib/autogen/connector/)"
"J4","1","LED board PWM","Connector_PinHeader_2.54mm:PinHeader_1x04_P2.54mm_Vertical","","","Generic connector, single row, 01x04, script generated (kicad-library-utils/schlib/autogen/connector/)"
"J5","1","Battery JST-PH","Connector_JST:JST_PH_S2B-PH-K_1x02_P2.00mm_Horizontal","JST","S2B-PH-K-S","Battery lead connector, pin 1 = cell positive. The 18650 sits in the enclosure cradle."
"L1","1","2.2uH","Inductor_SMD:L_Coilcraft_LPS3314","Coilcraft","","Shielded inductor 2.2 uH, Coilcraft LPS3314 series, Isat above 0.5 A"
"Q1","1","FS8205A","Package_SO:TSSOP-8_4.4x3mm_P0.65mm","Fortune Semiconductor","FS8205A","Dual N-channel MOSFET, common drain, 20 V, 6 A, 25 mOhm at 4.5 V, TSSOP-8"
"Q2","1","AO3401A","Package_TO_SOT_SMD:SOT-23","Alpha & Omega","AO3401A","-4.0A Id, -30V Vds, P-Channel MOSFET, SOT-23"
"R1,R5,R6,R15,R22,R23","6","100k","Resistor_SMD:R_0603_1608Metric","","","Resistor"
"R2","1","68k","Resistor_SMD:R_0603_1608Metric","","","Resistor"
"R3","1","3.0k 1%","Resistor_SMD:R_0603_1608Metric","","","Resistor"
"R4","1","1.8k 1%","Resistor_SMD:R_0603_1608Metric","","","Resistor"
"R7,R9,R12","3","1k","Resistor_SMD:R_0603_1608Metric","","","Resistor"
"R8,R20,R21","3","100R","Resistor_SMD:R_0603_1608Metric","","","Resistor"
"R10,R11","2","2.2M 1%","Resistor_SMD:R_0603_1608Metric","","","Resistor"
"R13,R14","2","4.7k","Resistor_SMD:R_0603_1608Metric","","","Resistor"
"R16,R17","2","5.1k","Resistor_SMD:R_0603_1608Metric","","","Resistor"
"R18,R19","2","27R","Resistor_SMD:R_0603_1608Metric","","","Resistor"
"SW1","1","RESET","Button_Switch_SMD:SW_SPST_B3U-1000P","Omron","B3U-1000P","Push button switch, generic, two pins"
"SW2","1","USER","Button_Switch_SMD:SW_SPST_B3U-1000P","Omron","B3U-1000P","Push button switch, generic, two pins"
"TH1","1","NTC 10k","Resistor_SMD:R_0603_1608Metric","","","NTC thermistor 10k at 25 C, B 3380 K, 0603"
"TP1","1","+3V3","TestPoint:TestPoint_Pad_D1.0mm","","","test point"
"TP2","1","VSYS","TestPoint:TestPoint_Pad_D1.0mm","","","test point"
"TP3","1","VBAT","TestPoint:TestPoint_Pad_D1.0mm","","","test point"
"TP4","1","GND","TestPoint:TestPoint_Pad_D1.0mm","","","test point"
"TP5","1","UART_TX","TestPoint:TestPoint_Pad_D1.0mm","","","test point"
"TP6","1","UART_RX","TestPoint:TestPoint_Pad_D1.0mm","","","test point"
"TP7","1","VBUS","TestPoint:TestPoint_Pad_D1.0mm","","","test point"
"U1","1","BQ24074RGT","Package_DFN_QFN:VQFN-16-1EP_3x3mm_P0.5mm_EP1.6x1.6mm","Texas Instruments","BQ24074RGTR","USB-Friendly Li-Ion Battery Charger and Power-Path Management, VQFN-16"
"U2","1","TPS62740DSS","Package_SON:WSON-12-1EP_3x2mm_P0.5mm_EP1x2.65","Texas Instruments","TPS62740DSSR","360 nA Iq step-down converter, 300 mA, 1.8 V to 3.3 V selectable output, WSON-12 (DSS)"
"U3","1","DW01A","Package_TO_SOT_SMD:SOT-23-6","","DW01A","Overcharge, overcurrent and overdischarge protection IC for single cell lithium-ion/polymer battery"
"U4","1","MDBT50Q-1MV2","RF_Module:Raytac_MDBT50Q","Raytac","MDBT50Q-1MV2","Multiprotocol BLE/ANT/2.4 GHz/802.15.4 Cortex-M4F SoC, nRF52840 module"
"U5","1","SHT40-AD1B","Sensor_Humidity:Sensirion_DFN-4_1.5x1.5mm_P0.8mm_SHT4x_NoCentralPad","Sensirion","SHT40-AD1B-R2","Digital Humidity and Temperature Sensor, ±1%RH, ±0.1°C, I2C, 1.08-3.6V, 16bit, DFN-4"
"U6","1","TSL25911FN","OptoDevice:AMS_TSL25911FN","ams OSRAM","TSL25911FN","Light to digital converter, 2.7 to 3.6V Vdd, DFN-6"
"U7","1","USBLC6-2SC6","Package_TO_SOT_SMD:SOT-23-6","STMicroelectronics","USBLC6-2SC6","Very low capacitance ESD protection diode, 2 data-line, SOT-23-6"
"Y1","1","32.768kHz 9pF","Crystal:Crystal_SMD_3215-2Pin_3.2x1.5mm","Abracon","ABS07-32.768KHZ-9-T","32.768 kHz crystal, 9 pF load, +/-20 ppm, ESR 70 kOhm max, 3.2 x 1.5 mm"

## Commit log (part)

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2026-02-08 Initial commit: G.O.S. Phenotyping Platform v1.0
2026-02-08 docs: Expand interview prep script to 6879 lines with comprehensive file-by-file reference guide
2026-02-08 docs: Update README
2026-02-08 docs: Fix corrupted interview prep script with clean UTF-8 encoding
2026-02-15 docs: Add PCB layout preparation checklist for KiCad
2026-02-15 docs: Add PCB design AI prompt templates for hardware engineering
2026-02-15 docs: Expand PCB design reference with detailed engineering formulas, protection circuits, and stackup design
2026-02-15 docs: Add comprehensive G.O.S. PCB design specification with BOM, schematics, and layout strategy
2026-02-15 Update README to remove advisor details
    Removed project advisor information from README.
2026-02-17 v2.0: Redesign PCB spec with complete BOM, ESD protection, BQ24075 charger, and engineering insights
2026-02-17 fix: Resolve all critical/moderate issues from PCB spec validity audit
    - C1: nRF52840 package corrected from QFN-48 to aQFN-73
    - C2: AL8860 VIN warning added - must use LED_VIN (4.5V min), not VDD_3V3
    - C3: TPS62740 VSEL truth table added (all HIGH = 3.3V)
    - M1: Battery divider redesigned with P-MOSFET gate (zero standby drain)
    - M2: 32.768kHz crystal caps reverted to 6.8pF (Cstray~4pF per Nordic)
    - M3: nRF52840 thermal via pattern added (4x4 grid, 0.3mm drill)
2026-02-17 fix: Complete PCB doc validation — add missing BOM entries, fix bench_testing, correct block diagram
    - Added R1/R2 (1MOhm), Q4 (DMG2305UX), R30 (100kOhm), C33 (100nF) to BOM
    - Corrected block diagram: Boost -> Buck (TPS62740 is a buck converter)
    - Updated component count: ~70 line items, ~108 placed components
    - bench_testing.md: LDO -> TPS62740 buck regulator, 1.8V -> 1.3V at DEC4
2026-02-17 sync: Propagate PCB v2.0 changes to all affected project files
    - overlay: battery divider 100kOhm -> 1MOhm (gated via Q4 P-MOSFET)
    - power_mgmt.h: battery range 3.3V -> 3.0V (18650), discharge curve updated
    - hardware_specs.md: complete rewrite with correct BOM, charger, protection, power budget
    - nrf52840_pinout.md: added AIN0, P0.03 BAT_EN, TSL2591 INT, USB-C, SWD pins
2026-02-17 fix(pcb-spec): 12 datasheet-verified corrections to PCB design spec and docs
    PCB Design Specification (11 fixes):
    - BQ24075 ISET R8: 2kohm->1.2kohm (KISET=890, actual 742mA not 750mA)
    - RF matching: L2=10nH->L4=3.9nH per Nordic AN-032, C31=0.8pF ref added
    - Overlay quote: 100kohm->1Mohm to match actual gated divider
    - SHT4x cap ref: C11->C23 to match BOM table
    - DW01A ODP threshold: 2.5V->2.4V per DW01A datasheet
2026-02-17 fix: project-wide sync against PCB spec v2.0
    mechanical/enclosure_gen.scad:
    - PCB dims: 64x100mm (DK) -> 40x65mm (custom G.O.S. PCB per spec 12.1)
    - Header: DK/Dongle -> Custom G.O.S. PCB (nRF52840 aQFN-73)
    gateway/services/farm_sim.py:
    - Battery sim min clamp: 3200mV -> 3000mV (18650 useful floor)
    ml_engine/phenotyping.py:
